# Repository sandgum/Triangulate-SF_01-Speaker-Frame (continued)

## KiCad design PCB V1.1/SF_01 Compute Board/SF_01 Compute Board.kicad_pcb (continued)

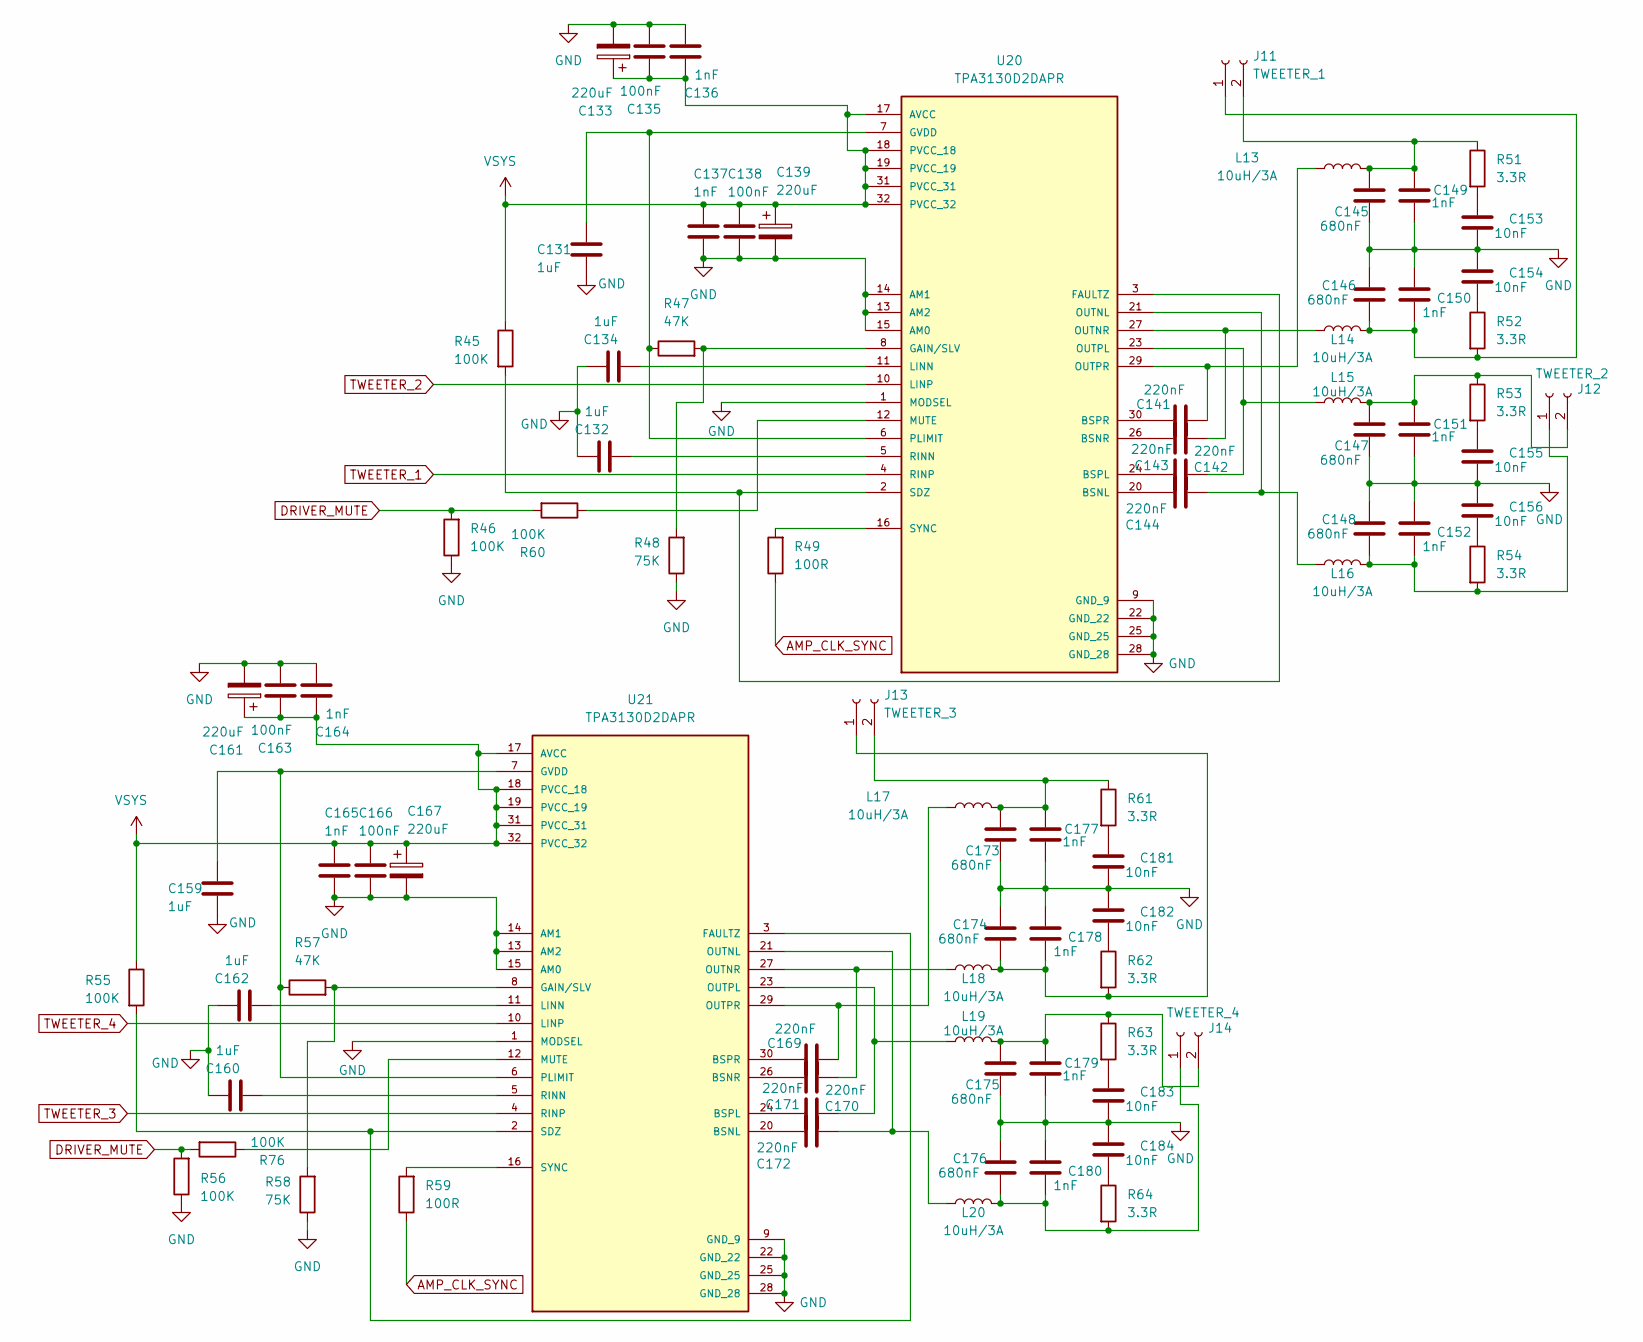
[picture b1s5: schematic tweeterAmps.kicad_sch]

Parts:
C131, C132, C134, C159, C160, C162: 1uF; C_0603_1608Metric
C133, C139, C161, C167: 220uF; CP_Elec_6.3x9.9
C135, C138, C163, C166: 100nF; C_0603_1608Metric
C136, C137, C149, C150, C151, C152, C164, C165, C177, C178, C179, C180: 1nF; C_0603_1608Metric
C141, C142, C143, C144, C169, C170, C171, C172: 220nF; C_0603_1608Metric
C145, C146, C147, C148, C173, C174, C175, C176: 680nF; C_0603_1608Metric
C153, C154, C155, C156, C181, C182, C183, C184: 10nF; C_0603_1608Metric
J11: TWEETER_1; JST_XH_S2B-XH-A-1_1x02_P2.50mm_Horizontal
J12: TWEETER_2; JST_XH_S2B-XH-A-1_1x02_P2.50mm_Horizontal
J13: TWEETER_3; JST_XH_S2B-XH-A-1_1x02_P2.50mm_Horizontal
J14: TWEETER_4; JST_XH_S2B-XH-A-1_1x02_P2.50mm_Horizontal
L13, L14, L15, L16, L17, L18, L19, L20: 10uH/3A; L_APV_ANR4020
R45, R46, R55, R56, R60, R76: 100K; R_0603_1608Metric
R47, R57: 47K; R_0603_1608Metric
R48, R58: 75K; R_0603_1608Metric
R49, R59: 100R; R_0603_1608Metric
R51, R52, R53, R54, R61, R62, R63, R64: 3.3R; R_0805_2012Metric
U20, U21: TPA3130D2DAPR; SOP65P810X115-32N; PARTREV G

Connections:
AMP_CLK_SYNC: R49.1, R59.1; also elsewhere on the board
DRIVER_MUTE: R46.2, R56.2, R60.2, R76.2; also elsewhere on the board
unnamed: C153.2, R51.2
unnamed: C154.1, R52.1
unnamed: C155.2, R53.2
unnamed: C156.1, R54.1
unnamed: C181.2, R61.2
unnamed: C182.1, R62.1
unnamed: C183.2, R63.2
unnamed: C184.1, R64.1
unnamed: C146.1, C150.1, J11.1, L14.2, R52.2
unnamed: C145.2, C149.2, J11.2, L13.2, R51.1
unnamed: C148.1, C152.1, J12.1, L16.2, R54.2
unnamed: C147.2, C151.2, J12.2, L15.2, R53.1
unnamed: C174.1, C178.1, J13.1, L18.2, R62.2
unnamed: C173.2, C177.2, J13.2, L17.2, R61.1
unnamed: C176.1, C180.1, J14.1, L20.2, R64.2
unnamed: C175.2, C179.2, J14.2, L19.2, R63.1
unnamed: C144.1, U20.20 (BSNL)
unnamed: C142.1, U20.26 (BSNR)
unnamed: C143.1, U20.24 (BSPL)
unnamed: C141.1, U20.30 (BSPR)
unnamed: R45.2, U20.2 (SDZ), U20.3 (FAULTZ)
unnamed: R47.2, R48.2, U20.8 (GAIN/SLV)
unnamed: C131.2, R47.1, U20.6 (PLIMIT), U20.7 (GVDD)
unnamed: C134.2, U20.11 (LINN)
unnamed: R60.1, U20.12 (MUTE)
unnamed: C144.2, L16.1, U20.21 (OUTNL)
unnamed: C142.2, L14.1, U20.27 (OUTNR)
unnamed: C143.2, L15.1, U20.23 (OUTPL)
unnamed: C141.2, L13.1, U20.29 (OUTPR)
unnamed: C132.2, U20.5 (RINN)
unnamed: R49.2, U20.16 (SYNC)
unnamed: C172.1, U21.20 (BSNL)
unnamed: C170.1, U21.26 (BSNR)
unnamed: C171.1, U21.24 (BSPL)
unnamed: C169.1, U21.30 (BSPR)
unnamed: R55.2, U21.2 (SDZ), U21.3 (FAULTZ)
unnamed: R57.2, R58.2, U21.8 (GAIN/SLV)
unnamed: C159.2, R57.1, U21.6 (PLIMIT), U21.7 (GVDD)
unnamed: C162.2, U21.11 (LINN)
unnamed: R76.1, U21.12 (MUTE)
unnamed: C172.2, L20.1, U21.21 (OUTNL)
unnamed: C170.2, L18.1, U21.27 (OUTNR)
unnamed: C171.2, L19.1, U21.23 (OUTPL)
unnamed: C169.2, L17.1, U21.29 (OUTPR)
unnamed: C160.2, U21.5 (RINN)
unnamed: R59.2, U21.16 (SYNC)
TWEETER_1: U20.4 (RINP); also elsewhere on the board
TWEETER_2: U20.10 (LINP); also elsewhere on the board
TWEETER_3: U21.4 (RINP); also elsewhere on the board
TWEETER_4: U21.10 (LINP); also elsewhere on the board
VSYS: C133.1, C135.1, C136.1, C137.1, C138.1, C139.1, C161.1, C163.1, C164.1, C165.1, C166.1, C167.1, R45.1, R55.1, U20.17 (AVCC), U20.18 (PVCC_18), U20.19 (PVCC_19), U20.31 (PVCC_31), U20.32 (PVCC_32), U21.17 (AVCC), U21.18 (PVCC_18), U21.19 (PVCC_19), U21.31 (PVCC_31), U21.32 (PVCC_32); also elsewhere on the board

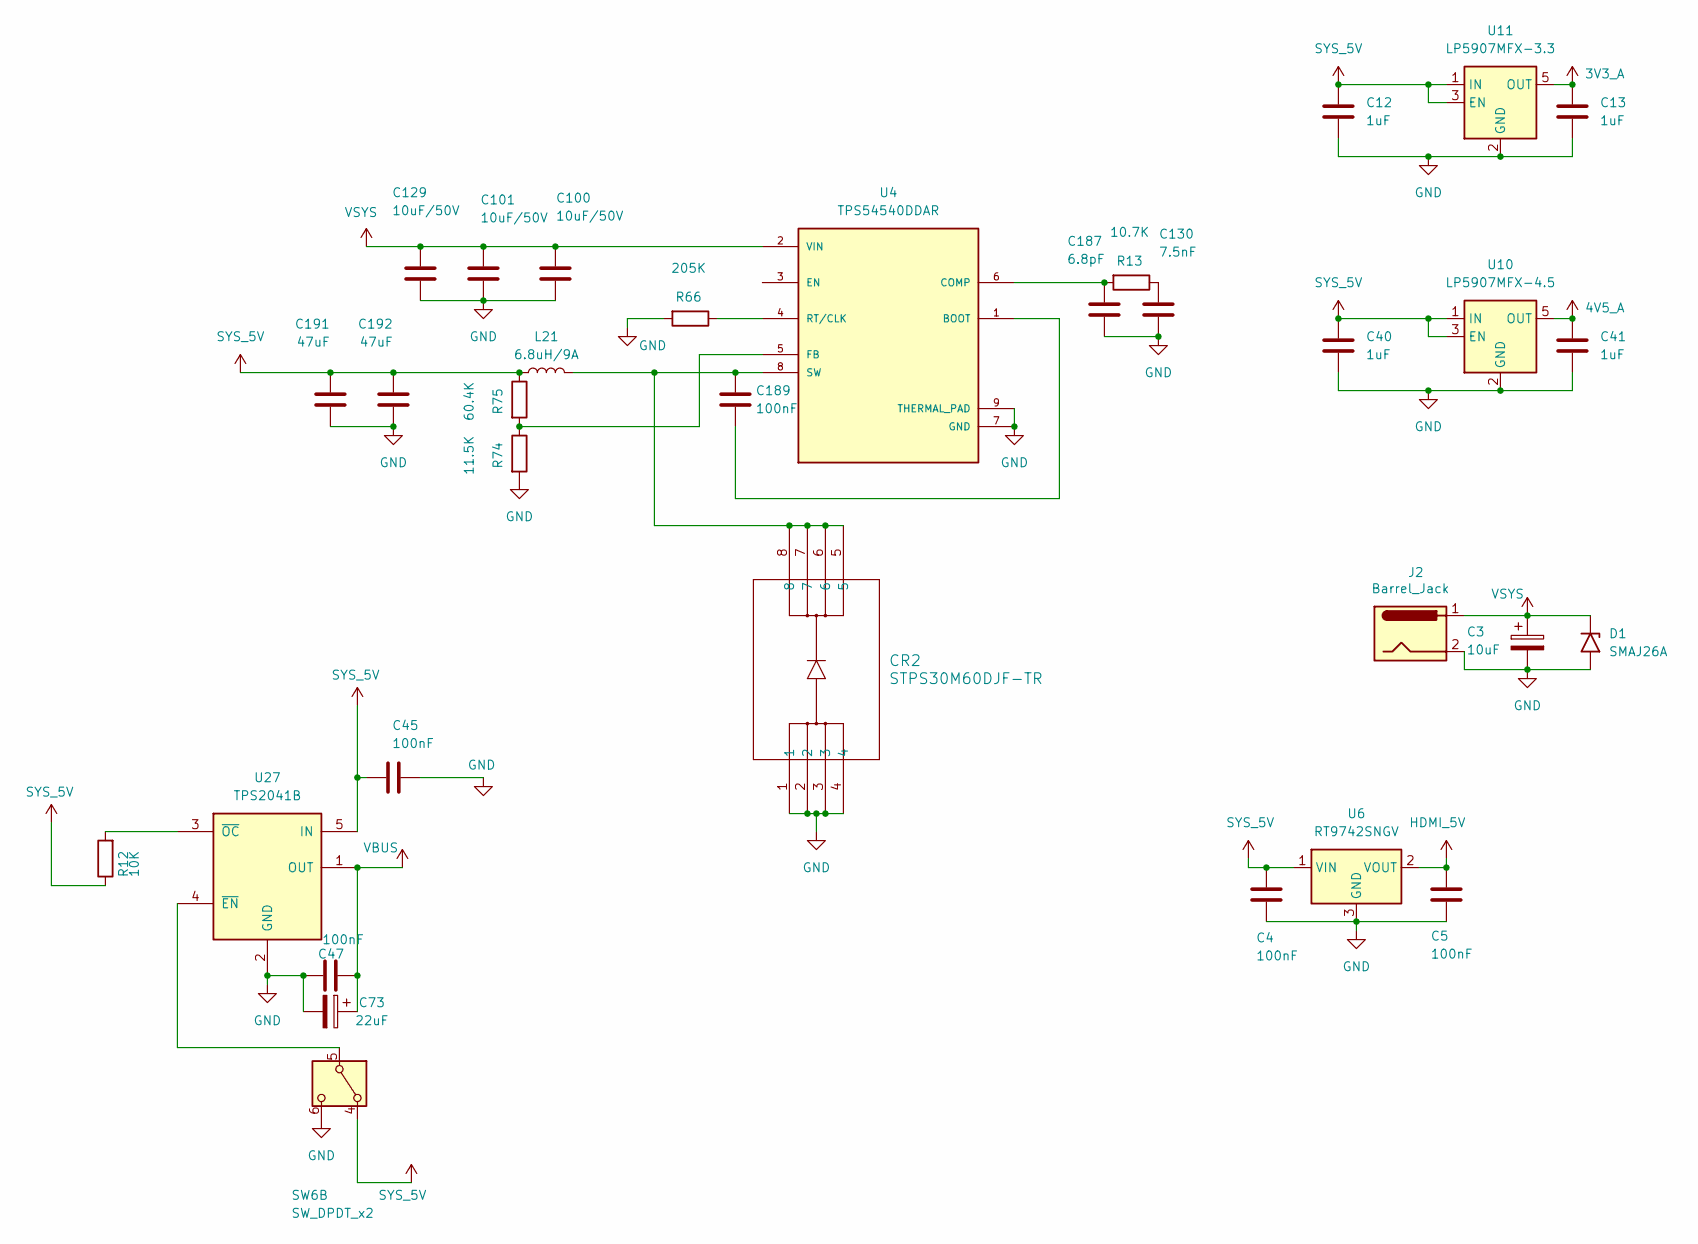
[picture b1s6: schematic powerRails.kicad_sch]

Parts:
C3: 10uF; CP_Elec_4x3
C4, C5, C45, C47, C189: 100nF; C_0603_1608Metric
C12, C13, C40, C41: 1uF; C_0603_1608Metric
C73: 22uF; CP_Elec_4x3
C100, C101, C129: 10uF/50V; C_1210_3225Metric
C130: 7.5nF; C_0603_1608Metric
C187: 6.8pF; C_0603_1608Metric
C191, C192: 47uF; C_1210_3225Metric
CR2: STPS30M60DJF-TR; POWERFLAT5X6_STM
D1: SMAJ26A; D_SMA
J2: Barrel_Jack; BarrelJack_SwitchcraftConxall_RAPC10U_Horizontal
L21: 6.8uH/9A; L_6.3x6.3_H3
R12: 10K; R_0603_1608Metric
R13: 10.7K; R_0603_1608Metric
R66: 205K; R_0603_1608Metric
R74: 11.5K; R_0603_1608Metric
R75: 60.4K; R_0603_1608Metric
SW6: SW_DPDT_x2; SW_DPDT_CK_JS202011JCQN
U4: TPS54540DDAR; CONV_TPS54540DDAR; PARTREV B
U6: RT9742SNGV; SOT-23-3
U10: LP5907MFX-4.5; SOT-23-5
U11: LP5907MFX-3.3; SOT-23-5
U27: TPS2041B; SOT-23-5

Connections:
3V3_A: C13.2, U11.5 (OUT); also elsewhere on the board
HDMI_5V: C5.1, U6.2 (VOUT); also elsewhere on the board
unnamed: C130.1, R13.1
unnamed: SW6.5 (B), U27.4 (~EN)
unnamed: C189.2, U4.1 (BOOT)
unnamed: C187.1, R13.2, U4.6 (COMP)
unnamed: R74.1, R75.2, U4.5 (FB)
unnamed: R66.1, U4.4 (RT/CLK)
unnamed: C189.1, CR2.5, CR2.6, CR2.7, CR2.8, L21.2, U4.8 (SW)
unnamed: R12.2, U27.3 (~OC)
VBUS: C47.2, C73.1, U27.1 (OUT); also elsewhere on the board
VSYS: C3.1, C100.1, C101.1, C129.1, D1.1 (A1), J2.1, U4.2 (VIN); also elsewhere on the board

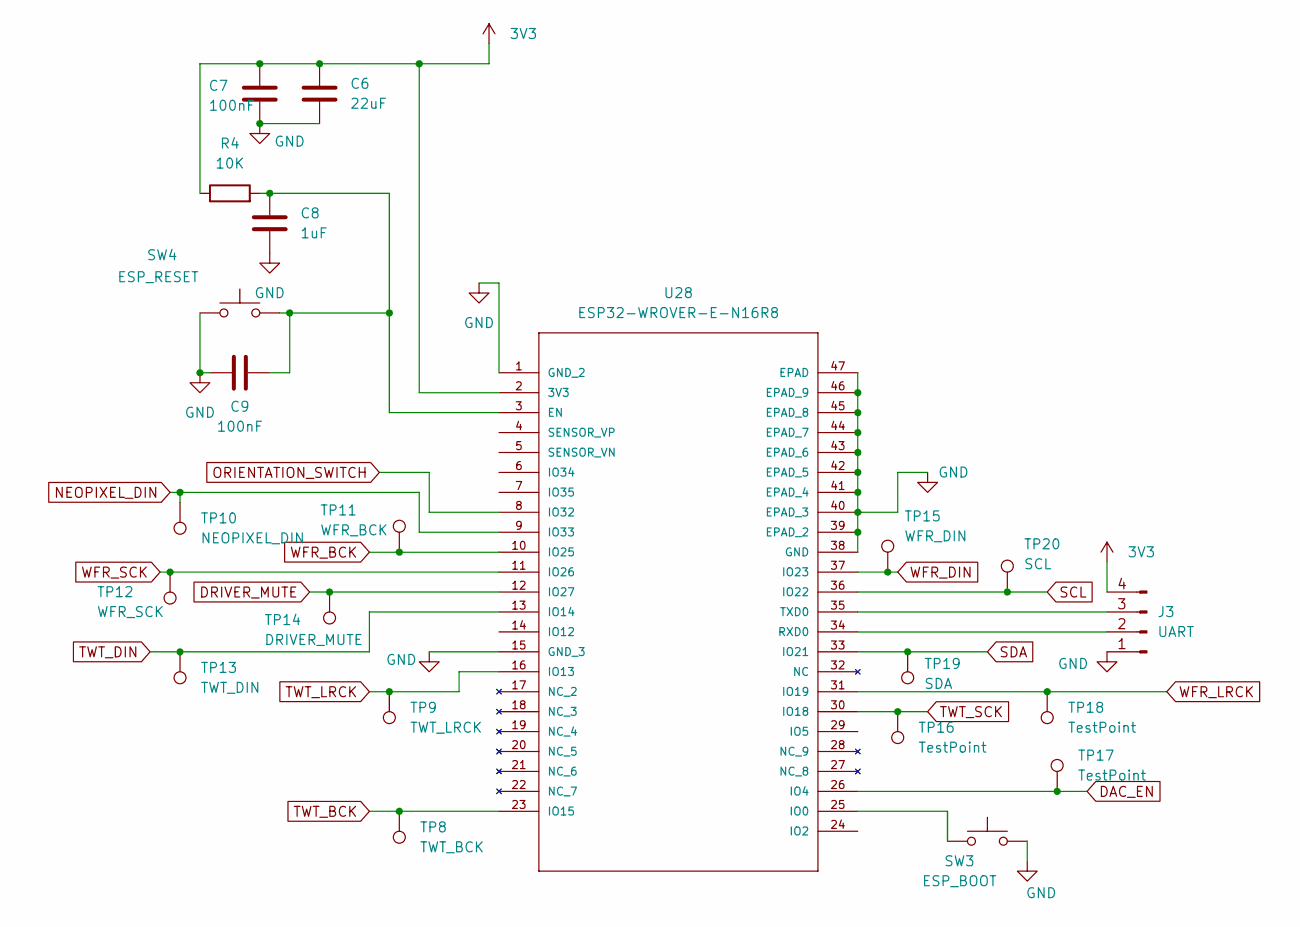
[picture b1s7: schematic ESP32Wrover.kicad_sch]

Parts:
C6: 22uF; C_0603_1608Metric
C7, C9: 100nF; C_0603_1608Metric
C8: 1uF; C_0603_1608Metric
J3: UART; PinHeader_1x04_P2.54mm_Vertical
R4: 10K; R_0603_1608Metric
SW3: ESP_BOOT; SW_Push_1P1T-SH_NO_CK_KMR2xxG
SW4: ESP_RESET; SW_Push_1P1T-SH_NO_CK_KMR2xxG
TP8: TWT_BCK; TestPoint_Pad_3.0x3.0mm
TP9: TWT_LRCK; TestPoint_Pad_3.0x3.0mm
TP10: NEOPIXEL_DIN; TestPoint_Pad_D2.5mm
TP11: WFR_BCK; TestPoint_Pad_3.0x3.0mm
TP12: WFR_SCK; TestPoint_Pad_3.0x3.0mm
TP13: TWT_DIN; TestPoint_Pad_3.0x3.0mm
TP14: DRIVER_MUTE; TestPoint_Pad_D2.5mm
TP15: WFR_DIN; TestPoint_Pad_3.0x3.0mm
TP16, TP17, TP18: TestPoint; TestPoint_Pad_D2.5mm
TP19: SDA; TestPoint_Pad_3.0x3.0mm
TP20: SCL; TestPoint_Pad_3.0x3.0mm
U28: ESP32-WROVER-E-N16R8; ESP32-WROVER-E_EXP; MANUFACTURER_PART_NUMBER ESP32-WROVER-E-N16R8

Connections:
3V3: C6.1, C7.1, J3.4, R4.1, U28.2 (3V3); also elsewhere on the board
DAC_EN: TP17.1 (1_1), U28.26 (IO4); also elsewhere on the board
DRIVER_MUTE: TP14.1 (1_1), U28.12 (IO27); also elsewhere on the board
NEOPIXEL_DIN: TP10.1 (1_1), U28.9 (IO33); also elsewhere on the board
unnamed: J3.2, U28.34 (RXD0)
unnamed: J3.3, U28.35 (TXD0)
unnamed: C8.2, C9.1, R4.2, SW4.2, U28.3 (EN)
unnamed: SW3.1, U28.25 (IO0)
ORIENTATION_SWITCH: U28.8 (IO32); also elsewhere on the board
SCL: TP20.1 (1_1), U28.36 (IO22); also elsewhere on the board
SDA: TP19.1 (1_1), U28.33 (IO21); also elsewhere on the board
TWT_BCK: TP8.1 (1_1), U28.23 (IO15); also elsewhere on the board
TWT_DIN: TP13.1 (1_1), U28.13 (IO14); also elsewhere on the board
TWT_LRCK: TP9.1 (1_1), U28.16 (IO13); also elsewhere on the board
TWT_SCK: TP16.1 (1_1), U28.30 (IO18); also elsewhere on the board
WFR_BCK: TP11.1 (1_1), U28.10 (IO25); also elsewhere on the board
WFR_DIN: TP15.1 (1_1), U28.37 (IO23); also elsewhere on the board
WFR_LRCK: TP18.1 (1_1), U28.31 (IO19); also elsewhere on the board
WFR_SCK: TP12.1 (1_1), U28.11 (IO26); also elsewhere on the board

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
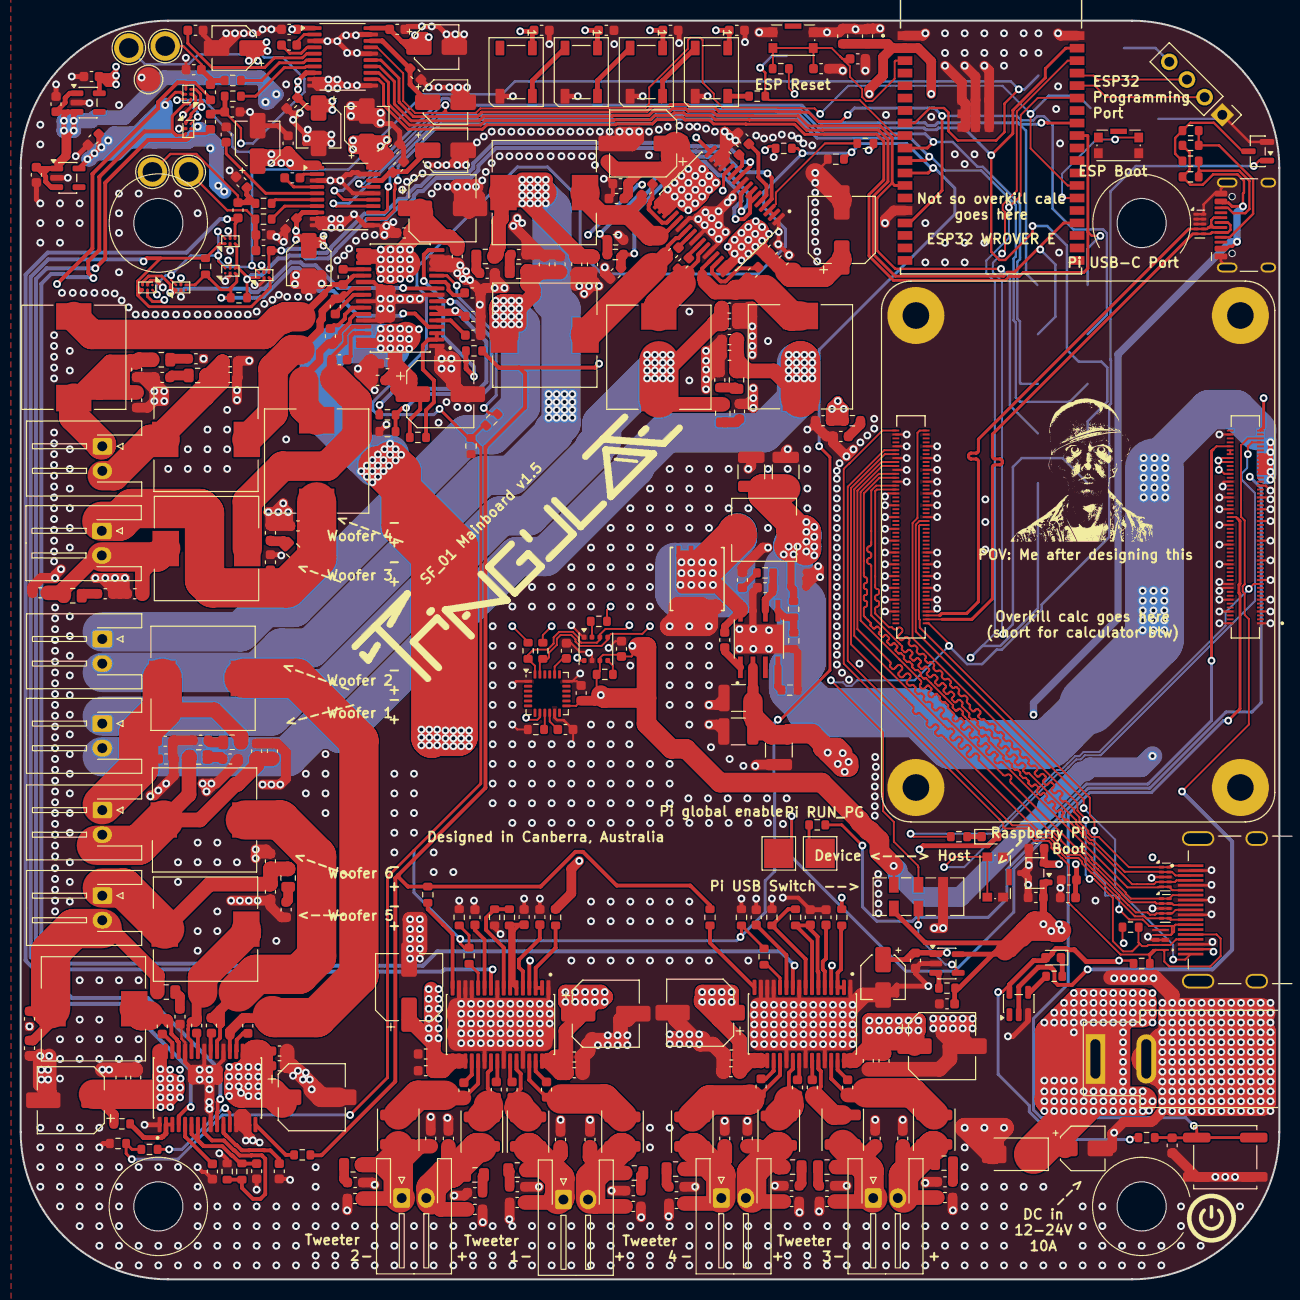
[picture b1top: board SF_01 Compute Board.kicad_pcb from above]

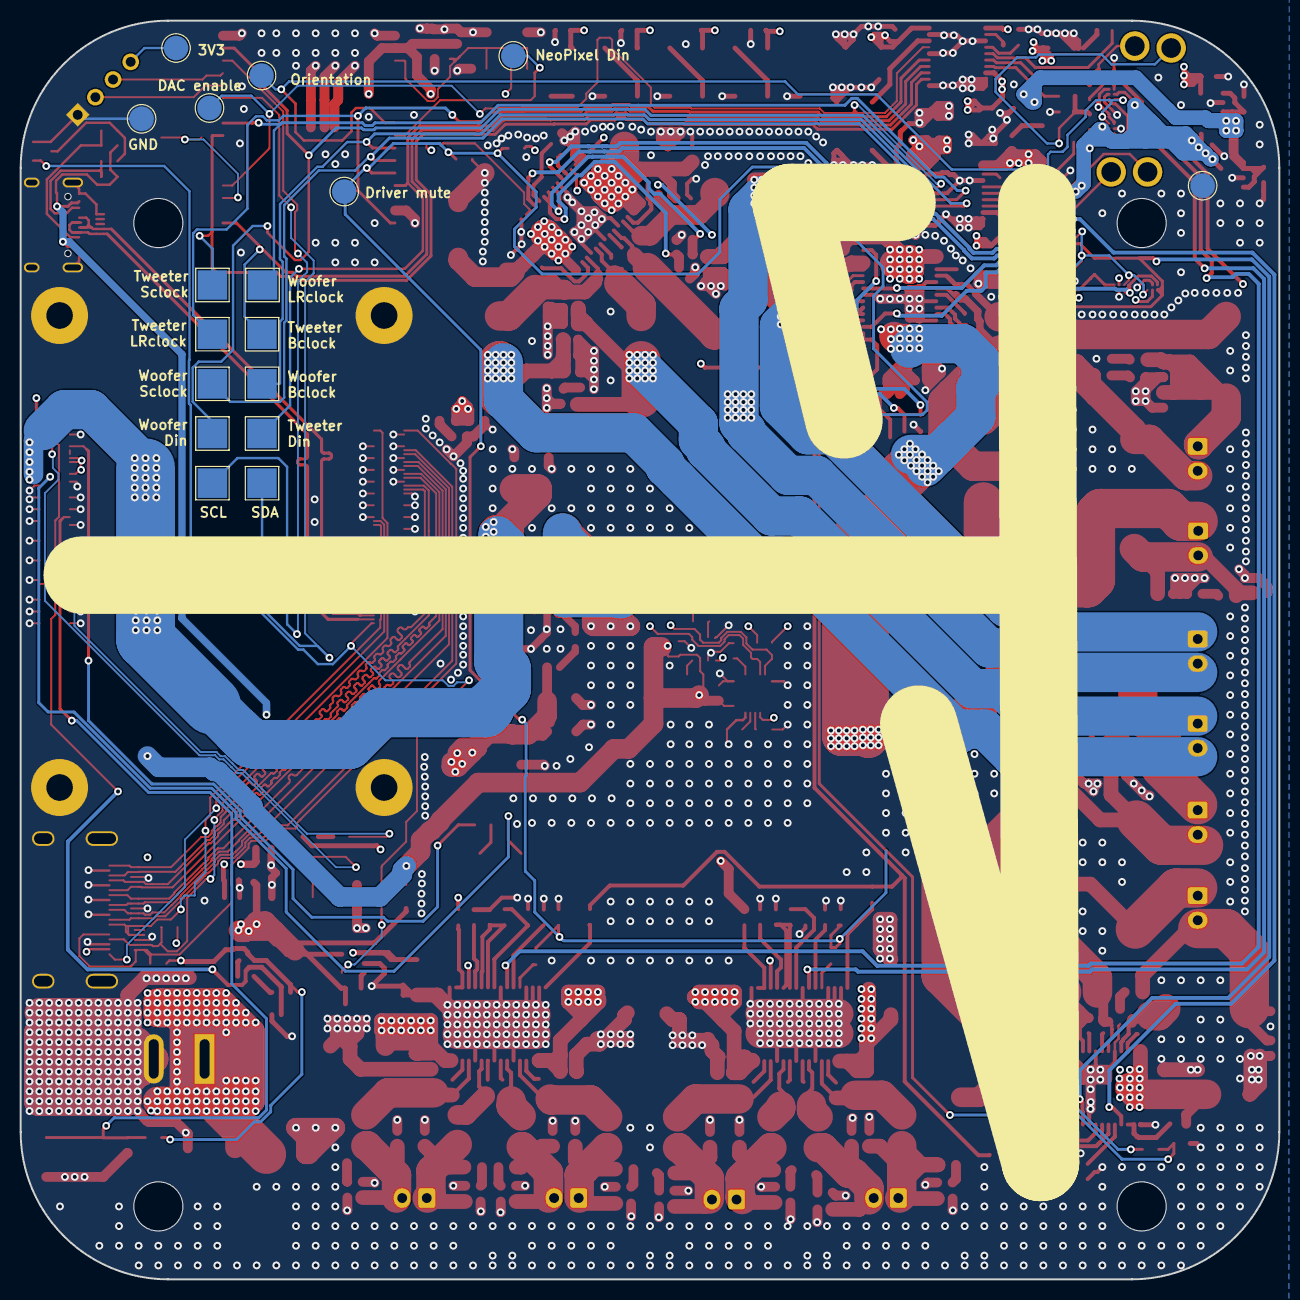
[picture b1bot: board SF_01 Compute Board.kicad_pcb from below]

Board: 4 copper layers, 128.0 x 128.0 mm, 367 parts (17 on the bottom side), 214 nets.

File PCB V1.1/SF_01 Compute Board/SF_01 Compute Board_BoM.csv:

"Reference","Qty","Value","DNP","Exclude from BOM","Exclude from Board"
"C1,C4,C5,C7,C9,C14,C17,C19,C23,C26,C28,C31,C34,C37,C38,C39,C42,C43,C45,C47,C50,C53,C72,C80,C81,C106,C109,C135,C138,C163,C166,C185,C186","33","100nF","","",""
"C2,C8,C12,C13,C44,C46,C48,C75,C76,C77,C102,C103,C105,C131,C132,C134,C157,C158,C159,C160,C162,C188,C190","23","1uF","","",""
"C3,C15,C16,C18,C22,C25,C27,C32,C33,C40","10","10uF","","",""
"C6,C73","2","22uF","","",""
"C10,C11,C35,C36,C71","5","2.2nF","","",""
"C20,C21,C29,C30","4","2.2uF","","",""
"C24,C63,C64,C69,C70,C96,C97,C98,C99,C123,C124,C125,C126,C153,C154,C155,C156,C181,C182,C183,C184","21","10nF","","",""
"C41","1","10uF (Tantalum)","","",""
"C49,C52,C61,C62,C67,C68,C79,C82,C92,C93,C94,C95,C107,C108,C119,C120,C121,C122,C127,C128,C136,C137,C140,C149,C150,C151,C152,C164,C165,C168,C177,C178,C179,C180","34","1nF","","",""
"C51,C54,C78,C83,C104,C110,C133,C139,C161,C167","10","220uF","","",""
"C55,C56,C57,C58,C84,C85,C86,C87,C111,C112,C113,C114,C141,C142,C143,C144,C169,C170,C171,C172","20","220nF","","",""
"C59,C60,C65,C66,C88,C89,C90,C91,C115,C116,C117,C118,C145,C146,C147,C148,C173,C174,C175,C176","20","680nF","","",""
"CR1","1","SP3010-04UTG","","",""
"D1","1","SMAJ33CA","","",""
"D2,D5,D6,D7","4","WS2812B","","",""
"D3,D4","2","LED","","",""
"J1","1","SS-53200-001","","",""
"J2","1","Barrel_Jack","","",""
"J3","1","UART","","",""
"J5","1","SUBWOOFER_1","","",""
"J6","1","SUBWOOFER_2","","",""
"J7","1","SUBWOOFER_3","","",""
"J8","1","SUBWOOFER_4","","",""
"J9","1","SUBWOOFER_5","","",""
"J10","1","SUBWOOFER_6","","",""
"J11","1","TWEETER_1","","",""
"J12","1","TWEETER_2","","",""
"J13","1","TWEETER_3","","",""
"J14","1","TWEETER_4","","",""
"J15","1","USB_C_Receptacle_USB2.0_16P","","",""
"L1,L2,L3,L4,L5,L6,L7,L8,L9,L10,L11,L12","12","10uH/10A","","",""
"L13,L14,L15,L16,L17,L18,L19,L20","8","10uH/3A","","",""
"R1,R2","2","2.2K","","",""
"R3,R65","2","5.1K","","",""
"R4,R12,R25,R44,R49,R59,R67,R68,R69,R70,R71","11","10K","","",""
"R5,R6,R72,R73","4","1K","","",""
"R8,R9,R10,R11","4","470R","","",""
"R14","1","220R","","",""
"R15,R21,R22,R23,R24,R31,R32,R33,R34,R40,R41,R42,R43,R51,R52,R53,R54,R61,R62,R63,R64","21","3.3R","","",""
"R16,R17,R18,R20,R26,R27,R30,R35,R36,R39,R45,R46,R50,R55,R56,R60","16","100K","","",""
"R19","1","20K","","",""
"R28,R37,R47,R57","4","47K","","",""
"R29,R38,R48,R58","4","75K","","",""
"SW1","1","POWER","","",""
"SW2","1","PI_BOOT","","",""
"SW3","1","ESP_BOOT","","",""
"SW4","1","ESP_RESET","","",""
"SW6","1","SW_DPDT_x2","","",""
"U1","1","CM4102008","","",""
"U2,U3,U7","3","TPD4E02B04DQA","","",""
"U5,U14","2","PCM5102A","","",""
"U6","1","RT9742SNGV","","",""
"U8,U9","2","74LVC1G07","","",""
"U11","1","LP5907MFX-3.3","","",""
"U12,U13,U15,U16,U24,U25,U26","7","TS5A3159AYZPR","","",""
"U17,U18,U19","3","TPA3116D2DAD","","",""
"U20,U21","2","TPA3130D2DAPR","","",""
"U22","1","MPU-6050","","",""
"U23","1","BME680","","",""
"U27","1","TPS2041B","","",""
"U28","1","ESP32-WROVER-E-N16R8","","",""
"VR1","1","LM1085ISX-5.0_NOPB","","",""

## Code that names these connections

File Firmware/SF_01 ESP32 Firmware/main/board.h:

/*
 * board.h — SF_01 Compute Board pin map.
 *
 * Pin numbers are taken directly from the KiCad netlist of
 * "PCB V1.1/SF_01 Compute Board", module U28 (ESP32-WROVER-E-N16R8).
 * The bring-up devboard uses the same GPIO numbers, wired to the
 * matching test points, so one binary runs on both.
 *
 *   signal        GPIO   U28 pin   test point
 *   WFR_BCK        25      10        TP11
 *   WFR_LRCK       19      31        TP18
 *   WFR_DIN        23      37        TP15
 *   WFR_SCK        26      11        TP12
 *   TWT_BCK        15      23        TP8
 *   TWT_LRCK       13      16        TP9
 *   TWT_DIN        14      13        TP13
 *   TWT_SCK        18      30        TP16
 *   DAC_EN          4      26        TP17
 *   DRIVER_MUTE    27      12        TP14
 */
#pragma once

#include "driver/gpio.h"

/* Woofer / mid-bass DAC (U14) */
#define PIN_WFR_BCK      GPIO_NUM_25
#define PIN_WFR_LRCK     GPIO_NUM_19
#define PIN_WFR_DIN      GPIO_NUM_23
#define PIN_WFR_SCK      GPIO_NUM_26

/* Tweeter DAC (U5) */
#define PIN_TWT_BCK      GPIO_NUM_15
#define PIN_TWT_LRCK     GPIO_NUM_13
#define PIN_TWT_DIN      GPIO_NUM_14
#define PIN_TWT_SCK      GPIO_NUM_18

/*
 * DAC_EN drives XSMT (pin 17) on BOTH PCM5102As in parallel.
 * PCM5102A: XSMT low = soft mute, high = soft un-mute.
 */
#define PIN_DAC_EN       GPIO_NUM_4
#define DAC_UNMUTED      1
#define DAC_MUTED        0

/*
 * DRIVER_MUTE drives MUTE (pin 12) on all five amplifiers
 * (U17/U18/U19 TPA3116D2, U20/U21 TPA3130D2) through the 100 k
 * series resistors TI requires when the driver slews faster than
 * 10 V/ms (SLOS708G abs-max table, note 2).
 * TPA31xx: MUTE high = outputs Hi-Z, low = outputs enabled.
 */
#define PIN_DRIVER_MUTE  GPIO_NUM_27
#define AMPS_MUTED       1
#define AMPS_UNMUTED     0

/* I2C sensors (BME680, MPU-6050) — not used by the audio path yet. */
#define PIN_I2C_SDA      GPIO_NUM_21
#define PIN_I2C_SCL      GPIO_NUM_22

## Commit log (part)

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2026-06-24 Add devlog entry for digital picture frame design
    Documented the design process for a digital picture frame with integrated audio system, detailing component selection and design challenges.
2026-06-24 Document subwoofer box design in devlog 2
    Added details about the design and construction of the subwoofer box, including specifications and structural features.
2026-06-24 Update JOURNAL.md with devlog 3
    Added details about the design and assembly of the digital picture frame, including speaker system specifications and 3D printing considerations.
2026-06-25 Designed the PCB Schematic
2026-06-25 Changed Audio Multiplexer Circuit, Routed more
2026-06-26 Added USB Host control, Routed 1st amplifier
2026-06-26 Routed 2nd Subwoofer Amplifier
2026-06-26 Finished Routing 2nd Amplifier, started routing 3rd
2026-06-26 Enhance README with detailed project description
    Expanded the README with detailed descriptions of the SF_01 digital picture frame, including its features, layout, images, and schematics.
2026-06-26 Added Renders of Enclosure
2026-06-27 Finished the PCB!
2026-06-28 Finishing touches to PCB, add enclosure CAD files
2026-06-28 Update README with PCB layout and 3D model images
    Added PCB layout images and sections to README.
2026-06-28 Added PCB Version 1.1 with ESP32 WROVER E
2026-06-28 Started Firmware Project Using A2DP Template
2026-06-28 Revise circuit and PCB layout images in README
    Updated circuit images and PCB layout in README.
2026-06-28 Add Bill Of Materials section to README
    Added Bill Of Materials section with detailed component list including part numbers, manufacturers, quantities, prices, and descriptions.
2026-06-28 Added BoM and Production Files
2026-06-28 Document design process for SF_01 digital frame
    Added detailed devlogs documenting the design and assembly process of the SF_01 digital picture frame, including subwoofer box design, splitting frame for 3D printing, mounting options, and PCB schem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
2026-06-28 Add multiple devlogs for SF_01 project
    Updated JOURNAL.md to include additional devlogs detailing the design and assembly of a digital picture frame with integrated audio system, subwoofer box design, and PCB schematic development.
2026-06-28 Add new devlogs for SF_01 project updates
    Updated the JOURNAL.md file to include new devlogs detailing the design and development process for the SF_01 digital picture frame and audio system.
2026-06-28 Consolidate devlogs into JOURNAL.md
    Merged multiple devlogs into a single document, preserving detailed descriptions of the design and development process for the SF_01 digital picture frame and audio system.
2026-06-28 Update README with AI usage information
    Added clarification on AI usage in project.
